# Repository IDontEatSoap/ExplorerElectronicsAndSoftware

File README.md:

# ExplorerElectronicsAndSoftware
This is where I keep the Electronics and Software for my overlander motorhome

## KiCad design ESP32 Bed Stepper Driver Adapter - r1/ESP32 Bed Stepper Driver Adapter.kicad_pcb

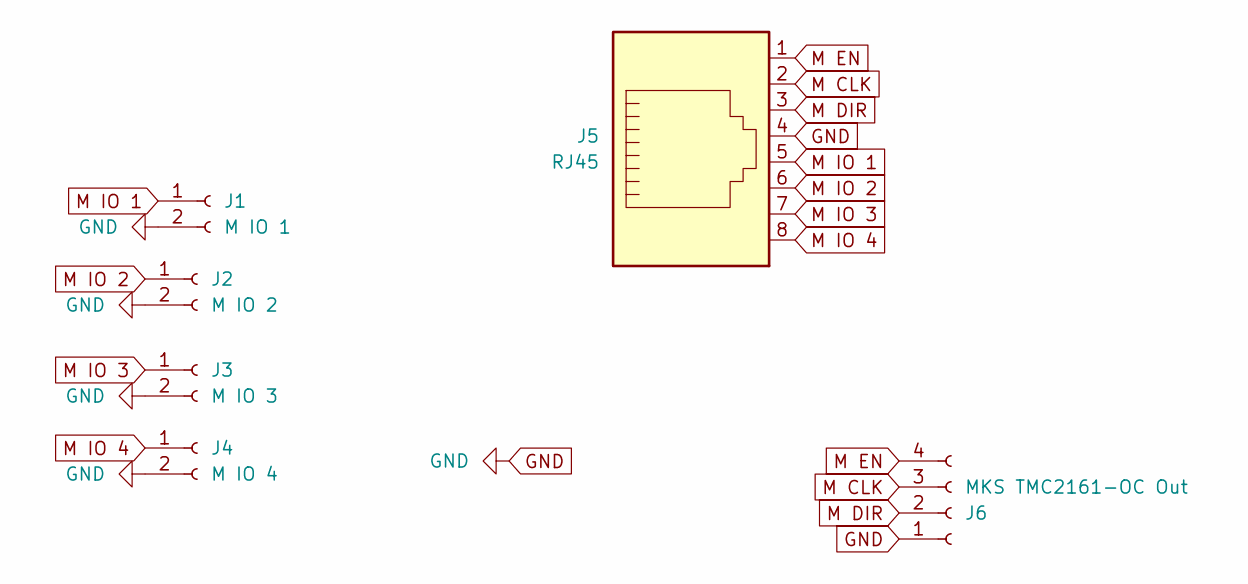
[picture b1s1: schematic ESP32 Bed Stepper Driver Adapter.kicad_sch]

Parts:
J1: M IO 1; JST_XH_B2B-XH-A_1x02_P2.50mm_Vertical
J2: M IO 2; JST_XH_B2B-XH-A_1x02_P2.50mm_Vertical
J3: M IO 3; JST_XH_B2B-XH-A_1x02_P2.50mm_Vertical
J4: M IO 4; JST_XH_B2B-XH-A_1x02_P2.50mm_Vertical
J5: RJ45; RJ458N3S
J6: MKS TMC2161-OC Out; JST_XH_B4B-XH-A_1x04_P2.50mm_Vertical

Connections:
GND: J1.2, J2.2, J3.2, J4.2, J5.4, J6.1
M CLK: J5.2, J6.3
M DIR: J5.3, J6.2
M EN: J5.1, J6.4
M IO 1: J1.1, J5.5
M IO 2: J2.1, J5.6
M IO 3: J3.1, J5.7
M IO 4: J4.1, J5.8

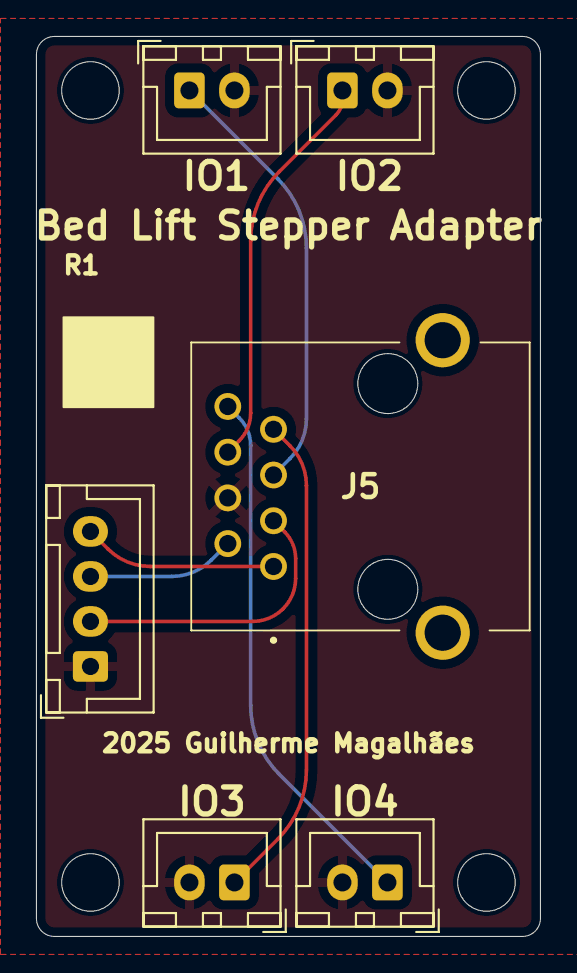
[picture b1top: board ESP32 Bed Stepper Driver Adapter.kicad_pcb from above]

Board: 2 copper layers, 28.0 x 50.0 mm, 6 parts (0 on the bottom side), 8 nets.

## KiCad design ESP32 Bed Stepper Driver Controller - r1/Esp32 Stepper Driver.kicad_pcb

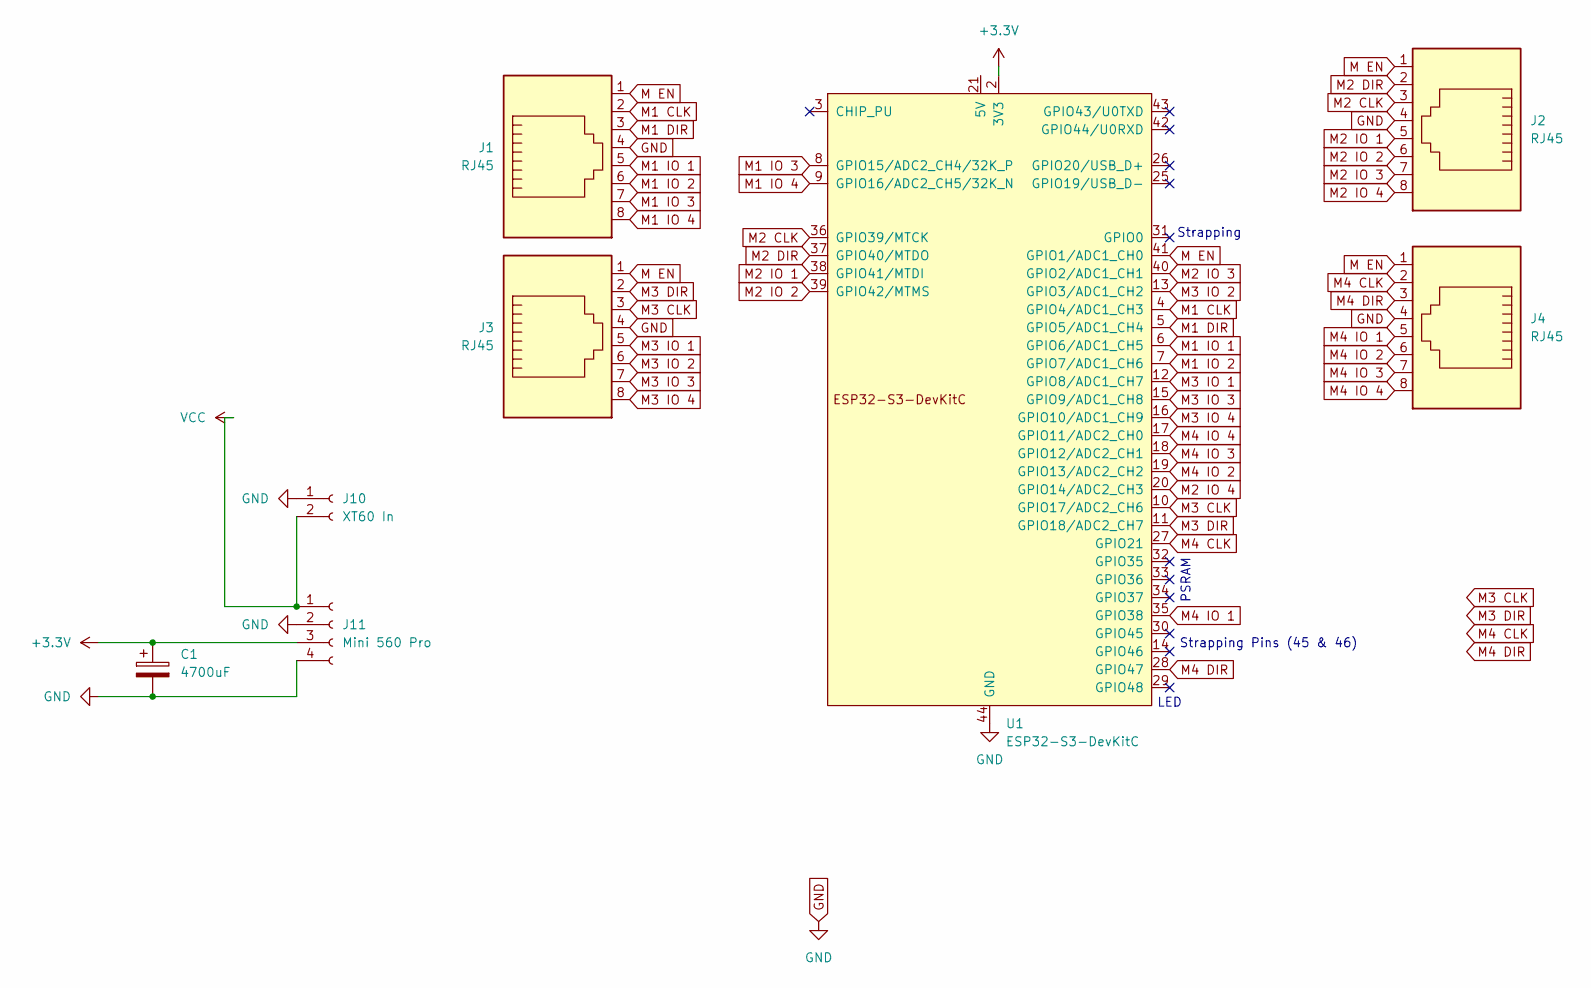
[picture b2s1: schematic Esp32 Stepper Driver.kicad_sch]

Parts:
C1: 4700uF; CP_Radial_D16.0mm_P7.50mm
J1, J2, J3, J4: RJ45; RJ458N3S
J10: XT60 In; AMASS_XT60PW-M_1x02_P7.20mm_Horizontal
J11: Mini 560 Pro
U1: ESP32-S3-DevKitC; ESP32-S3-DevKitC AliExpress

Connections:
+3.3V: C1.1, J11.3, U1.1 (3V3), U1.2 (3V3)
GND: C1.2, J1.4, J2.4, J3.4, J4.4, J10.1, J11.2, J11.4, U1.22 (GND), U1.23 (GND), U1.24 (GND), U1.44 (GND)
M1 CLK: J1.2, U1.4 (GPIO4/ADC1_CH3)
M1 DIR: J1.3, U1.5 (GPIO5/ADC1_CH4)
M1 IO 1: J1.5, U1.6 (GPIO6/ADC1_CH5)
M1 IO 2: J1.6, U1.7 (GPIO7/ADC1_CH6)
M1 IO 3: J1.7, U1.8 (GPIO15/ADC2_CH4/32K_P)
M1 IO 4: J1.8, U1.9 (GPIO16/ADC2_CH5/32K_N)
M2 CLK: J2.3, U1.36 (GPIO39/MTCK)
M2 DIR: J2.2, U1.37 (GPIO40/MTDO)
M2 IO 1: J2.5, U1.38 (GPIO41/MTDI)
M2 IO 2: J2.6, U1.39 (GPIO42/MTMS)
M2 IO 3: J2.7, U1.40 (GPIO2/ADC1_CH1)
M2 IO 4: J2.8, U1.20 (GPIO14/ADC2_CH3)
M3 CLK: J3.3, U1.10 (GPIO17/ADC2_CH6)
M3 DIR: J3.2, U1.11 (GPIO18/ADC2_CH7)
M3 IO 1: J3.5, U1.12 (GPIO8/ADC1_CH7)
M3 IO 2: J3.6, U1.13 (GPIO3/ADC1_CH2)
M3 IO 3: J3.7, U1.15 (GPIO9/ADC1_CH8)
M3 IO 4: J3.8, U1.16 (GPIO10/ADC1_CH9)
M4 CLK: J4.2, U1.27 (GPIO21)
M4 DIR: J4.3, U1.28 (GPIO47)
M4 IO 1: J4.5, U1.35 (GPIO38)
M4 IO 2: J4.6, U1.19 (GPIO13/ADC2_CH2)
M4 IO 3: J4.7, U1.18 (GPIO12/ADC2_CH1)
M4 IO 4: J4.8, U1.17 (GPIO11/ADC2_CH0)
M EN: J1.1, J2.1, J3.1, J4.1, U1.41 (GPIO1/ADC1_CH0)
VCC: J10.2, J11.1

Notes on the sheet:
LED
Strapping Pins (45 & 46)
PSRAM
Strapping

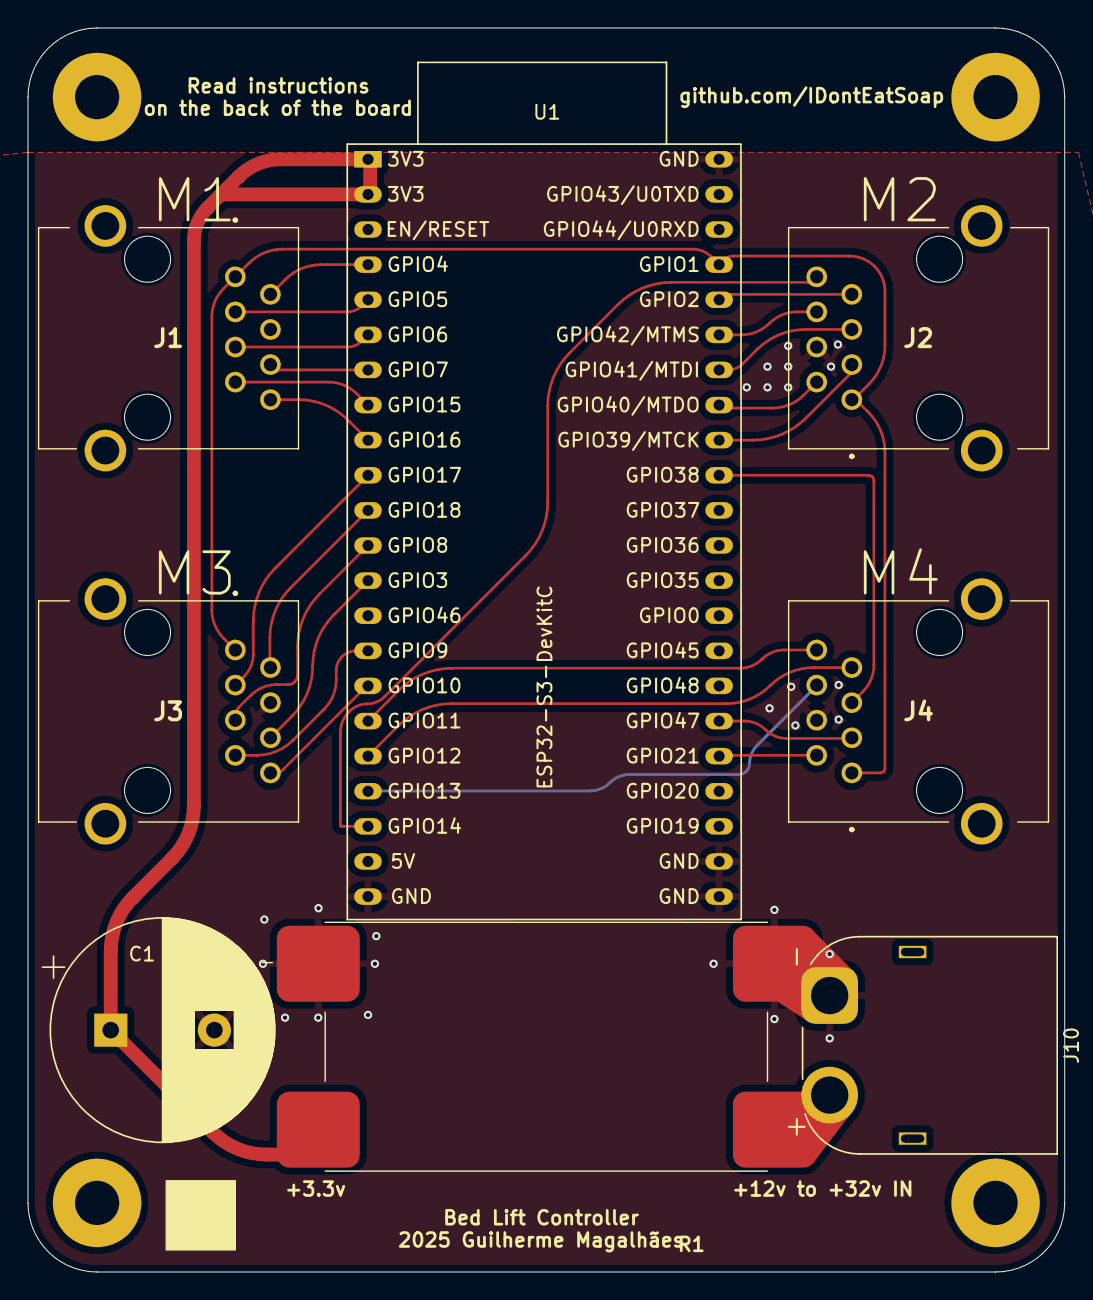
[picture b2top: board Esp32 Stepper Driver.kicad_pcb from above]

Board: 2 copper layers, 75.0 x 90.0 mm, 8 parts (0 on the bottom side), 28 nets.

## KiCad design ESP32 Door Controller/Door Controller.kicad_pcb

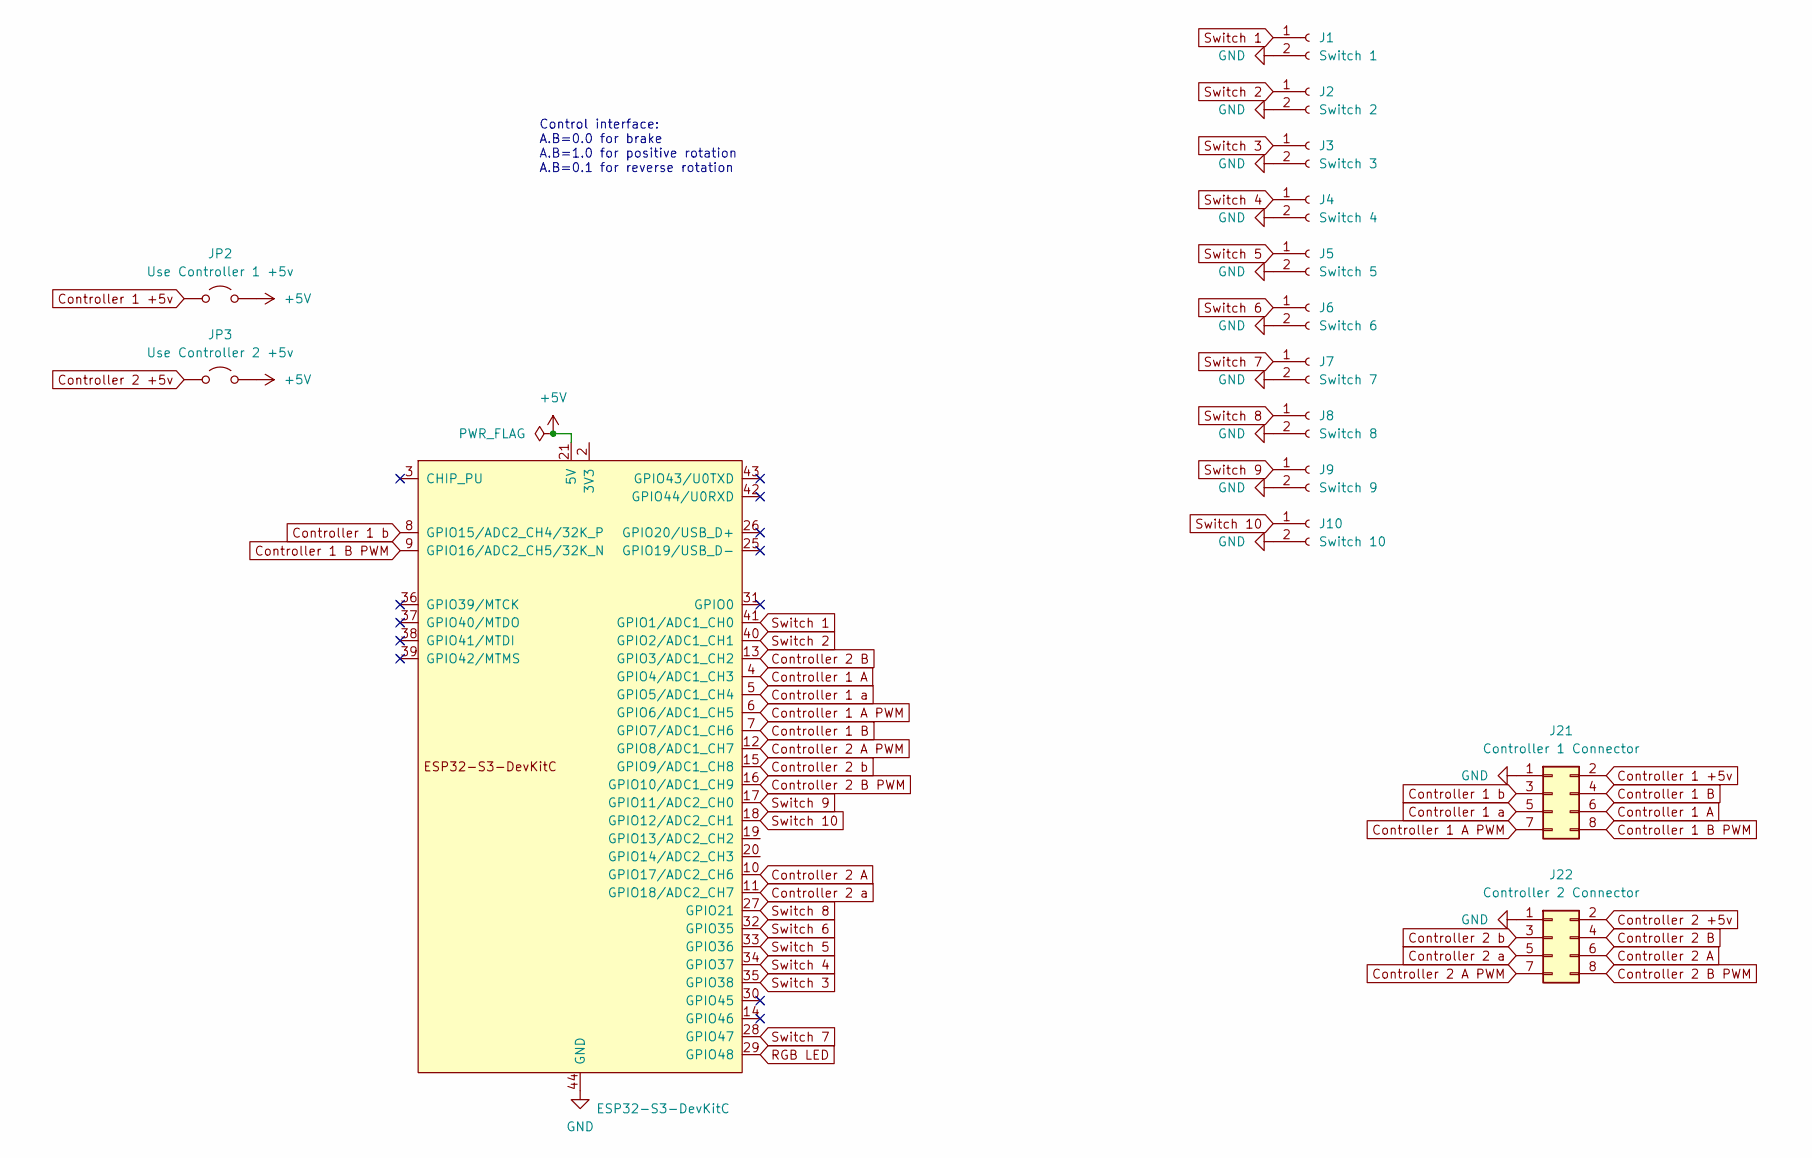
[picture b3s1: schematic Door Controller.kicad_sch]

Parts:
J1: Switch 1; JST_XH_B2B-XH-A_1x02_P2.50mm_Vertical
J2: Switch 2; JST_XH_B2B-XH-A_1x02_P2.50mm_Vertical
J3: Switch 3; JST_XH_B2B-XH-A_1x02_P2.50mm_Vertical
J4: Switch 4; JST_XH_B2B-XH-A_1x02_P2.50mm_Vertical
J5: Switch 5; JST_XH_B2B-XH-A_1x02_P2.50mm_Vertical
J6: Switch 6; JST_XH_B2B-XH-A_1x02_P2.50mm_Vertical
J7: Switch 7; JST_XH_B2B-XH-A_1x02_P2.50mm_Vertical
J8: Switch 8; JST_XH_B2B-XH-A_1x02_P2.50mm_Vertical
J9: Switch 9; JST_XH_B2B-XH-A_1x02_P2.50mm_Vertical
J10: Switch 10; JST_XH_B2B-XH-A_1x02_P2.50mm_Vertical
J21: Controller 1 Connector; IDC-Header_2x04_P2.54mm_Vertical
J22: Controller 2 Connector; IDC-Header_2x04_P2.54mm_Vertical
JP2: Use Controller 1 +5v; SolderJumper-2_P1.3mm_Open_RoundedPad1.0x1.5mm
JP3: Use Controller 2 +5v; SolderJumper-2_P1.3mm_Open_RoundedPad1.0x1.5mm
U1: ESP32-S3-DevKitC; ESP32-S3-DevKitC AliExpress

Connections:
+5V: JP2.2 (B), JP3.2 (B), U1.21 (5V)
Controller 1 +5v: J21.2, JP2.1 (A)
Controller 1 A: J21.6, U1.4 (GPIO4/ADC1_CH3)
Controller 1 A PWM: J21.7, U1.6 (GPIO6/ADC1_CH5)
Controller 1 B: J21.4, U1.7 (GPIO7/ADC1_CH6)
Controller 1 B PWM: J21.8, U1.9 (GPIO16/ADC2_CH5/32K_N)
Controller 1 a: J21.5, U1.5 (GPIO5/ADC1_CH4)
Controller 1 b: J21.3, U1.8 (GPIO15/ADC2_CH4/32K_P)
Controller 2 +5v: J22.2, JP3.1 (A)
Controller 2 A: J22.6, U1.10 (GPIO17/ADC2_CH6)
Controller 2 A PWM: J22.7, U1.12 (GPIO8/ADC1_CH7)
Controller 2 B: J22.4, U1.13 (GPIO3/ADC1_CH2)
Controller 2 B PWM: J22.8, U1.16 (GPIO10/ADC1_CH9)
Controller 2 a: J22.5, U1.11 (GPIO18/ADC2_CH7)
Controller 2 b: J22.3, U1.15 (GPIO9/ADC1_CH8)
GND: J1.2, J2.2, J3.2, J4.2, J5.2, J6.2, J7.2, J8.2, J9.2, J10.2, J21.1, J22.1, U1.22 (GND), U1.23 (GND), U1.24 (GND), U1.44 (GND)
unnamed: U1.1 (3V3), U1.2 (3V3)
RGB LED: U1.29 (GPIO48)
Switch 1: J1.1, U1.41 (GPIO1/ADC1_CH0)
Switch 2: J2.1, U1.40 (GPIO2/ADC1_CH1)
Switch 3: J3.1, U1.35 (GPIO38)
Switch 4: J4.1, U1.34 (GPIO37)
Switch 5: J5.1, U1.33 (GPIO36)
Switch 6: J6.1, U1.32 (GPIO35)
Switch 7: J7.1, U1.28 (GPIO47)
Switch 8: J8.1, U1.27 (GPIO21)
Switch 9: J9.1, U1.17 (GPIO11/ADC2_CH0)
Switch 10: J10.1, U1.18 (GPIO12/ADC2_CH1)

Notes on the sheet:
Control interface: A.B=0.0 for brake A.B=1.0 for positive rotation A.B=0.1 for reverse rotation

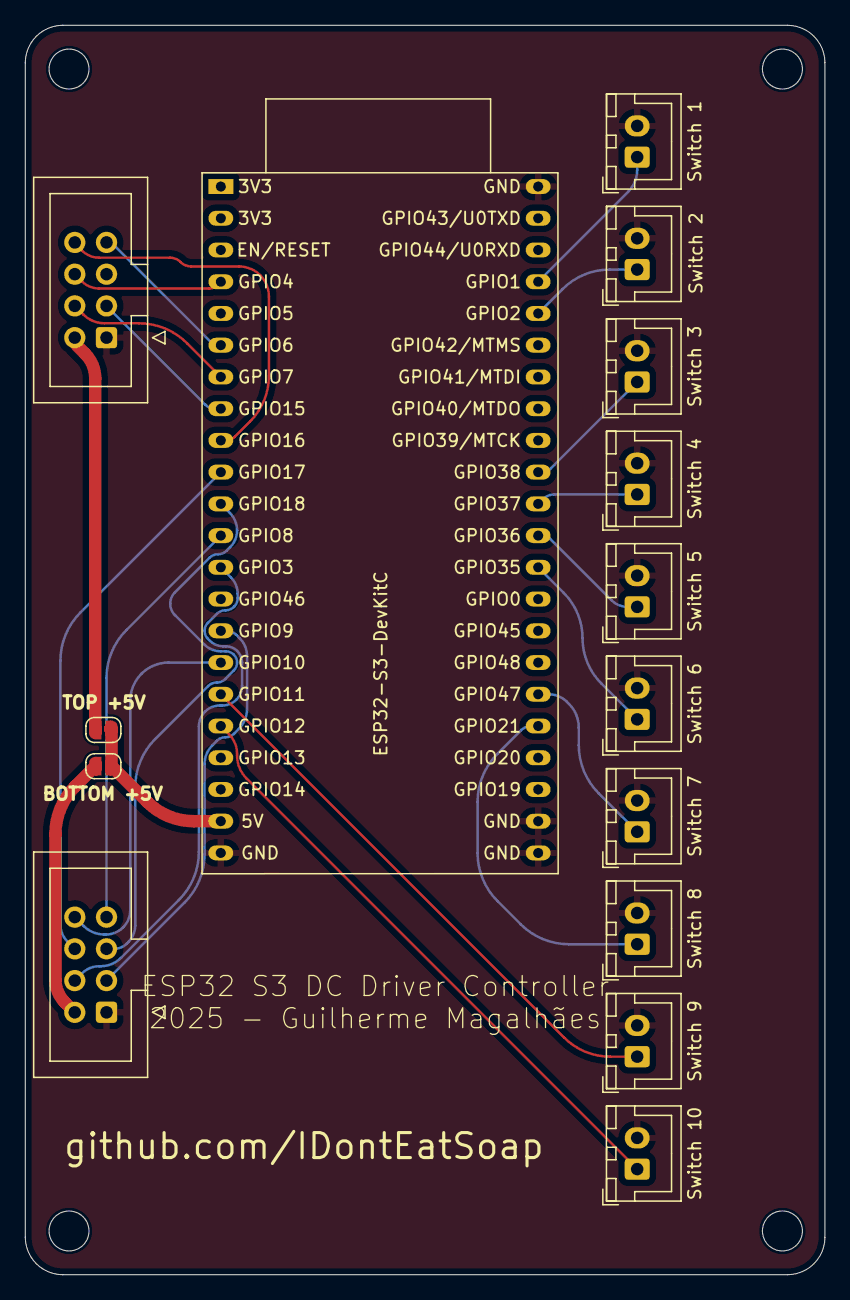
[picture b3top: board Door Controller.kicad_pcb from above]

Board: 2 copper layers, 64.0 x 100.0 mm, 19 parts (0 on the bottom side), 27 nets.

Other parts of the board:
h1, h2, h3, h4: MountingHole_3.2mm_M3

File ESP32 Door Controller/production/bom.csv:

Designator,Footprint,Quantity,Value,LCSC Part #
J1,JST_XH_B2B-XH-A_1x02_P2.50mm_Vertical,1,Switch 1,
J10,JST_XH_B2B-XH-A_1x02_P2.50mm_Vertical,1,Switch 10,
J2,JST_XH_B2B-XH-A_1x02_P2.50mm_Vertical,1,Switch 2,
J21,IDC-Header_2x04_P2.54mm_Vertical,1,Controller 1 Connector,
J22,IDC-Header_2x04_P2.54mm_Vertical,1,Controller 2 Connector,
J3,JST_XH_B2B-XH-A_1x02_P2.50mm_Vertical,1,Switch 3,
J4,JST_XH_B2B-XH-A_1x02_P2.50mm_Vertical,1,Switch 4,
J5,JST_XH_B2B-XH-A_1x02_P2.50mm_Vertical,1,Switch 5,
J6,JST_XH_B2B-XH-A_1x02_P2.50mm_Vertical,1,Switch 6,
J7,JST_XH_B2B-XH-A_1x02_P2.50mm_Vertical,1,Switch 7,
J8,JST_XH_B2B-XH-A_1x02_P2.50mm_Vertical,1,Switch 8,
J9,JST_XH_B2B-XH-A_1x02_P2.50mm_Vertical,1,Switch 9,
JP2,SolderJumper-2_P1.3mm_Open_RoundedPad1.0x1.5mm,1,Use Controller 1 +5v,
JP3,SolderJumper-2_P1.3mm_Open_RoundedPad1.0x1.5mm,1,Use Controller 2 +5v,
U1,ESP32-S3-DevKitC AliExpress,1,ESP32-S3-DevKitC,

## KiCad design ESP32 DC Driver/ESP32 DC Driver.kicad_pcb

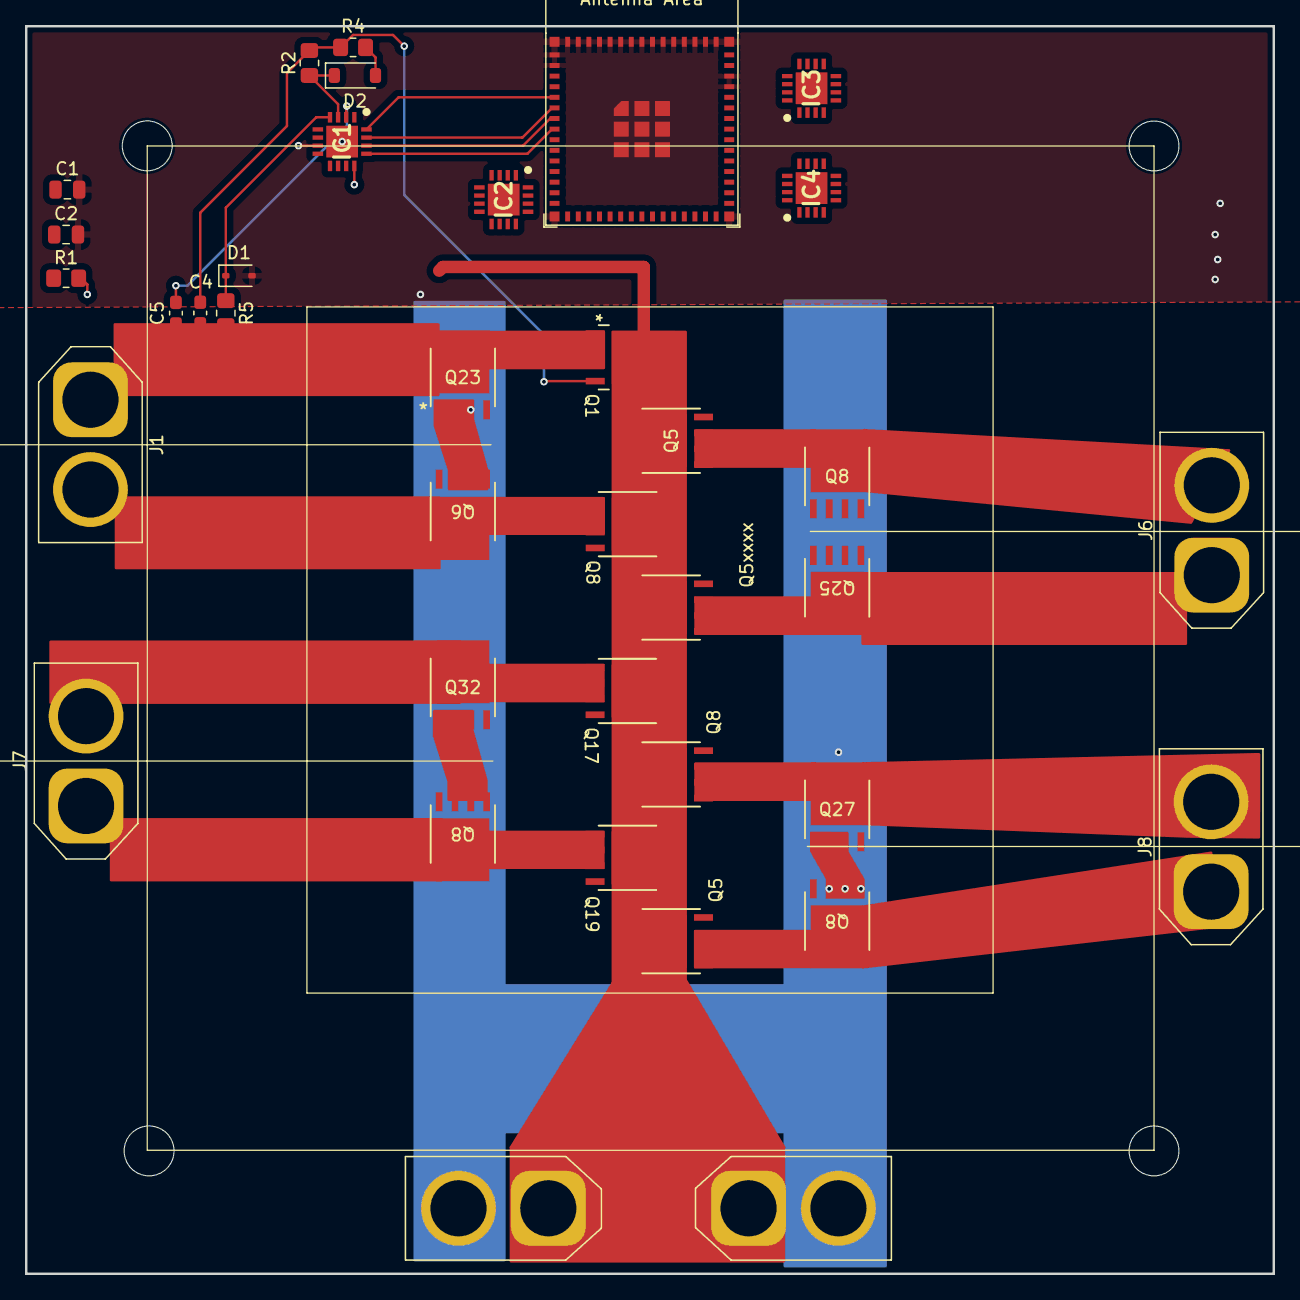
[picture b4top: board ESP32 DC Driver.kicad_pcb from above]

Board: 4 copper layers, 100.0 x 100.0 mm, 37 parts (0 on the bottom side), 35 nets.

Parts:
C1: 10uf; C_0805_2012Metric
C2: 1uf; C_0805_2012Metric
C4: 4700pF; C_0603_1608Metric_Pad1.08x0.95mm_HandSolder
C5: 10uf; C_0603_1608Metric_Pad1.08x0.95mm_HandSolder
D1: BAS316; D_SOD-323
D2: 1N4148; D_SOD-123
IC1, IC2, IC3, IC4: MIC4606-1YML-TR; QFN65P400X400X90-17N-D
J1: AMASS_XT60-M_1x02_P7.20mm_Vertical
J6, J7, J8: Output 1; AMASS_XT60-M_1x02_P7.20mm_Vertical
Q1, Q5, Q5#2, Q5xxxx, Q6, Q8, Q8#2, Q8#3, Q8#4, Q8#5, Q17, Q19, Q23, Q25, Q27, Q32: SQJ182EP-T1_GE3; PowerPAK_SO-8L_PPKSO8LWLA_Case_Outline_3_VIS
R1: 100k; R_0805_2012Metric_Pad1.20x1.40mm_HandSolder
R2: 18R; R_0805_2012Metric_Pad1.20x1.40mm_HandSolder
R4: 6.8R; R_0805_2012Metric_Pad1.20x1.40mm_HandSolder
R5: 3.3R; R_0805_2012Metric_Pad1.20x1.40mm_HandSolder
U2: ESP32-S3-MINI-1
xxx: AMASS_XT60-M_1x02_P7.20mm_Vertical
xxx#2: AMASS_XT60-M_1x02_P7.20mm_Vertical

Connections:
/AH1/G: C4.1, Q1.4, Q19.4, R2.2, R4.2
/AH1/S: C4.2, C5.2, J1.1, Q1.1, Q1.2, Q1.3, Q19.1, Q19.2, Q19.3, R5.2
/AH2/S: J6.2, Q5.1, Q5.2, Q5.3, Q8#2.5, Q23.5
/AH4/S: J8.2, Q8#4.1, Q8#4.2, Q8#4.3, Q27.5
/AL2/G: Q8#2.4, Q23.4
/BH1/G: Q8#3.4, Q17.4
/BH1/S: J1.2, Q6.5, Q8#3.1, Q8#3.2, Q8#3.3, Q17.1, Q17.2, Q17.3, Q32.5
/BH2/S: J6.1, Q5xxxx.1, Q5xxxx.2, Q5xxxx.3, Q25.5
/BH3/S: J7.1, Q8#5.5
/BH4/S: J8.1, Q5#2.1, Q5#2.2, Q5#2.3, Q8.5
/BL1/G: Q6.4, Q32.4
GND: C1.2, C2.2, D1.2 (A), IC1.7 (VSS), IC1.17 (GND), IC2.7 (VSS), IC2.17 (GND), IC3.7 (VSS), IC3.17 (GND), IC4.7 (VSS), IC4.17 (GND), Q6.1, Q6.2, Q6.3, Q8.1, Q8.2, Q8.3, Q8#2.1, Q8#2.2, Q8#2.3, Q8#5.1, Q8#5.2, Q8#5.3, Q23.1, Q23.2, Q23.3, Q25.1, Q25.2, Q25.3, Q27.1, Q27.2, Q27.3, Q32.1, Q32.2, Q32.3, U2.1 (GND), U2.2 (GND), U2.42 (GND), U2.43 (GND), U2.46 (GND), U2.47 (GND), U2.48 (GND), U2.49 (GND), U2.50 (GND), U2.51 (GND), U2.52 (GND), U2.53 (GND), U2.54 (GND), U2.55 (GND), U2.56 (GND), U2.57 (GND), U2.58 (GND), U2.59 (GND), U2.60 (GND), U2.61 (GND), U2.62 (GND), U2.63 (GND), U2.64 (GND), U2.65 (GND), xxx.2, xxx#2.2
Motor 1 AHI: IC1.16 (AHI), U2.5 (GPIO1/TOUCH1/ADC1_CH0)
Motor 1 ALI: IC1.15 (ALI), U2.6 (GPIO2/TOUCH2/ADC1_CH1)
Motor 1 BHI: IC1.13 (BHI), U2.8 (GPIO4/TOUCH4/ADC1_CH3)
Motor 1 BLI: IC1.14 (BLI), U2.7 (GPIO3/TOUCH3/ADC1_CH2)
Motor 2 AHI: IC2.16 (AHI), U2.9 (GPIO5/TOUCH5/ADC1_CH4)
Motor 2 ALI: IC2.15 (ALI), U2.10 (GPIO6/TOUCH6/ADC1_CH5)
Motor 2 BHI: IC2.13 (BHI), U2.12 (GPIO8/TOUCH8/ADC1_CH7/SUBSPICS1)
Motor 2 BLI: IC2.14 (BLI), U2.11 (GPIO7/TOUCH7/ADC1_CH6)
Motor 3 AHI: IC3.16 (AHI), U2.13 (GPIO9/TOUCH9/ADC1_CH8/FSPIHD/SUBSPIHD)
Motor 3 ALI: IC3.15 (ALI), U2.14 (GPIO10/TOUCH10/ADC1_CH9/FSPICS0/FSPIIO4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)
Motor 3 BHI: IC3.13 (BHI), U2.16 (GPIO12/TOUCH12/ADC2_CH1/FSPICLK/FSPIIO6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)
Motor 3 BLI: IC3.14 (BLI), U2.15 (GPIO11/TOUCH11/ADC2_CH0/FSPID/FSPIIO5/S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)
Motor 4 AHI: IC4.16 (AHI), U2.17 (GPIO13/TOUCH13/ADC2_CH2/FSPIQ/FSPIIO7/S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)
Motor 4 ALI: IC4.15 (ALI), U2.18 (GPIO14/TOUCH14/ADC2_CH3/FSPIWP/FSPIDQS/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)
Motor 4 BHI: IC4.13 (BHI), U2.22 (GPIO18/U1RXD/ADC2_CH7/CLK_OUT3)
Motor 4 BLI: IC4.14 (BLI), U2.21 (GPIO17/U1TXD/ADC2_CH6)
unnamed: D1.1 (K), IC1.4 (AHS), R5.1
unnamed: D2.2 (A), R4.1
unnamed: D2.1 (K), IC1.3 (AHO), R2.1
unnamed: C5.1, IC1.2 (AHB)
unnamed: IC1.12 (EN), R1.2
VBUS: Q1.5, Q5.5, Q5#2.5, Q5xxxx.5, Q8#3.5, Q8#4.5, Q17.5, Q19.5
VDD: C1.1, C2.1, IC1.6 (VDD), IC2.6 (VDD), IC3.6 (VDD), IC4.6 (VDD), R1.1

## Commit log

2025-01-09 First PCB
2025-01-09 no message
2025-02-13 Progress
